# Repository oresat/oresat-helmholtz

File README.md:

# OreSat Helmholtz Cage

This repo contains design and operating instructions of a Helmholtz Cage, which uses the [Biot Savart Law](https://en.wikipedia.org/wiki/Biot%E2%80%93Savart_law) to get a desired magnetic field inside of an enclosed space using three pairs of perpendicular coils, one pair for each axis. Our fundamental purpose in doing this is to test cubesats' pointing and detumbling capabilities in LEO.

v2.0 is now underway, utilizing less hardware than v1.0. This is excellent news for everyone involved, as less parts means less things that can and will break. We are using a Raspberry Pi Pico to run it, with each set of coils getting their own motor driver, to drive the current, and a INA226 to monitor the current. A full schematic can be found [here](./controller-v2/helmholtz-controller-v2.kicad_sch). A PCB layout is in the works.

# Design Notes

**Status, design, and testing information can be found in the [OreSat Helmholtz Cage Design Notes](https://docs.google.com/document/d/1s9UlxD-V_3-_QfmXqKaY5oYsfC2GDHxeAkWD0VgjS5g/edit?tab=t.0).**

A seperate doc on the structure and design of the cage itself can be found [here](./docs/Open%20Source%20Document.docx). This doc is a bit out of date in some aspects, mainly the technical hardware, but serves as a good resource for cage construction and theory.

## Pictures
MCECS BETA Project 2018:

Current Build:

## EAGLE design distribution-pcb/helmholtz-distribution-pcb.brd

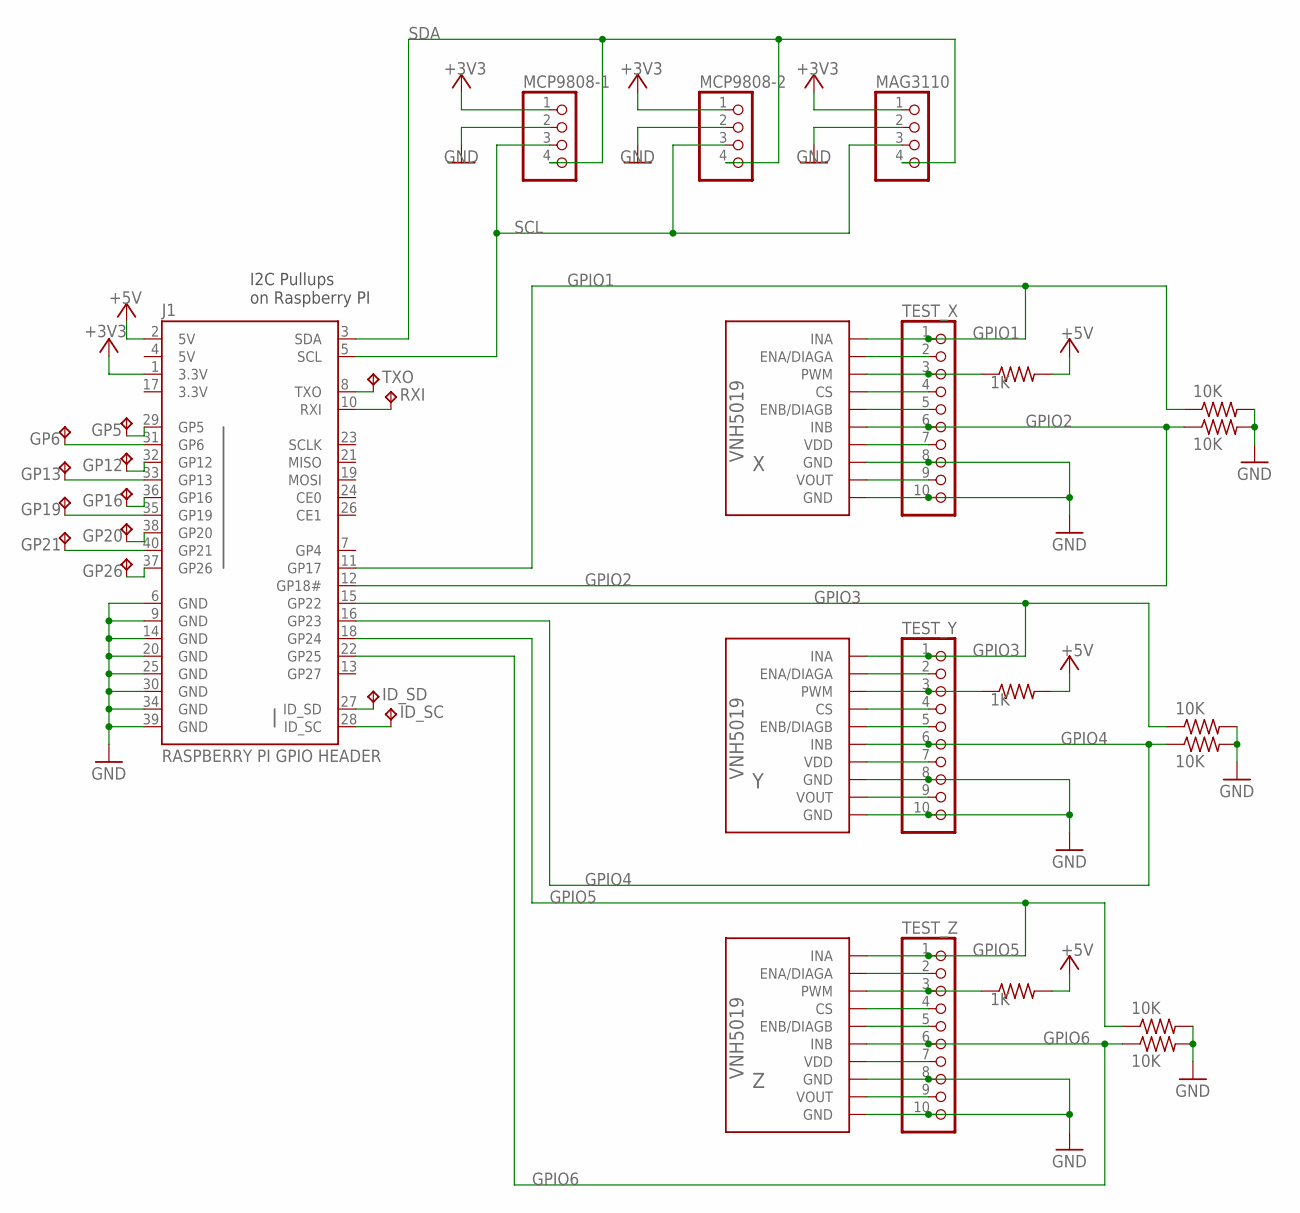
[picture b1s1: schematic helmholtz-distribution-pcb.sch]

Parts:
GP5, GP6, GP12, GP13, GP16, GP19, GP20, GP21, GP26: TPPAD1-13; P1-13
ID_SC: TPPAD1-13; P1-13
ID_SD: TPPAD1-13; P1-13
J1: RASPBERRYPI-40-PIN-GPIO_PTH; 2X20_SHROUDED
MAG3110: PINHD-1X4; 1X04
MCP9808-1, MCP9808-2: PINHD-1X4; 1X04
R2, R3, R9, R10, R16, R17: 10K; R0603
R7, R13, R20: 1K; R0603
RXI: TPPAD1-13; P1-13
TEST_X: PINHD-1X10; 1X10
TEST_Y: PINHD-1X10; 1X10
TEST_Z: PINHD-1X10; 1X10
TXO: TPPAD1-13; P1-13
X: VNH5019
Y: VNH5019
Z: VNH5019

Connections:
3.3V: J1.17 (3.3V)
5V: J1.4 (5V)
+3V3: J1.1 (3.3V), MAG3110.1, MCP9808-1.1, MCP9808-2.1
+5V: J1.2 (5V), R7.2, R13.2, R20.2
CS_X: TEST_X.4, X.CS
CS_Y: TEST_Y.4, Y.CS
CS_Z: TEST_Z.4, Z.CS
ENA/DIAGA_X: TEST_X.2, X.ENA/DIAGA
ENA/DIAGA_Y: TEST_Y.2, Y.ENA/DIAGA
ENA/DIAGA_Z: TEST_Z.2, Z.ENA/DIAGA
ENB/DIAGB_X: TEST_X.5, X.EBN/DIAGB (ENB/DIAGB)
ENB/DIAGB_Y: TEST_Y.5, Y.EBN/DIAGB (ENB/DIAGB)
ENB/DIAGB_Z: TEST_Z.5, Z.EBN/DIAGB (ENB/DIAGB)
GND: J1.6 (GND), J1.9 (GND), J1.14 (GND), J1.20 (GND), J1.25 (GND), J1.30 (GND), J1.34 (GND), J1.39 (GND), MAG3110.2, MCP9808-1.2, MCP9808-2.2, R2.2, R3.2, R9.2, R10.2, R16.2, R17.2, TEST_X.8, TEST_X.10, TEST_Y.8, TEST_Y.10, TEST_Z.8, TEST_Z.10, X.GND@1 (GND), X.GND@2 (GND), Y.GND@1 (GND), Y.GND@2 (GND), Z.GND@1 (GND), Z.GND@2 (GND)
GPIO1: J1.11 (GP17), R17.1, TEST_X.1, X.INA
GPIO2: J1.12 (GP18#), R16.1, TEST_X.6, X.INB
GPIO3: J1.15 (GP22), R10.1, TEST_Y.1, Y.INA
GPIO4: J1.16 (GP23), R9.1, TEST_Y.6, Y.INB
GPIO5: J1.18 (GP24), R3.1, TEST_Z.1, Z.INA
GPIO6: J1.22 (GP25), R2.1, TEST_Z.6, Z.INB
unnamed: GP26.TP, J1.37 (GP26)
unnamed: GP21.TP, J1.40 (GP21)
unnamed: GP20.TP, J1.38 (GP20)
unnamed: GP19.TP, J1.35 (GP19)
unnamed: GP16.TP, J1.36 (GP16)
unnamed: GP13.TP, J1.33 (GP13)
unnamed: GP12.TP, J1.32 (GP12)
unnamed: GP6.TP, J1.31 (GP6)
unnamed: GP5.TP, J1.29 (GP5)
unnamed: J1.8 (TXO), TXO.TP
unnamed: J1.10 (RXI), RXI.TP
unnamed: ID_SD.TP, J1.27 (ID_SD)
unnamed: ID_SC.TP, J1.28 (ID_SC)
PWM_X: R20.1, TEST_X.3, X.PWM
PWM_Y: R13.1, TEST_Y.3, Y.PWM
PWM_Z: R7.1, TEST_Z.3, Z.PWM
SCL: J1.5 (SCL), MAG3110.3, MCP9808-1.3, MCP9808-2.3
SDA: J1.3 (SDA), MAG3110.4, MCP9808-1.4, MCP9808-2.4
VDD_X: TEST_X.7, X.VDD
VDD_Y: TEST_Y.7, Y.VDD
VDD_Z: TEST_Z.7, Z.VDD
VOUT_X: TEST_X.9, X.VOUT
VOUT_Y: TEST_Y.9, Y.VOUT
VOUT_Z: TEST_Z.9, Z.VOUT

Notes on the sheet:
RASPBERRY PI GPIO HEADER
I2C Pullups on Raspberry PI

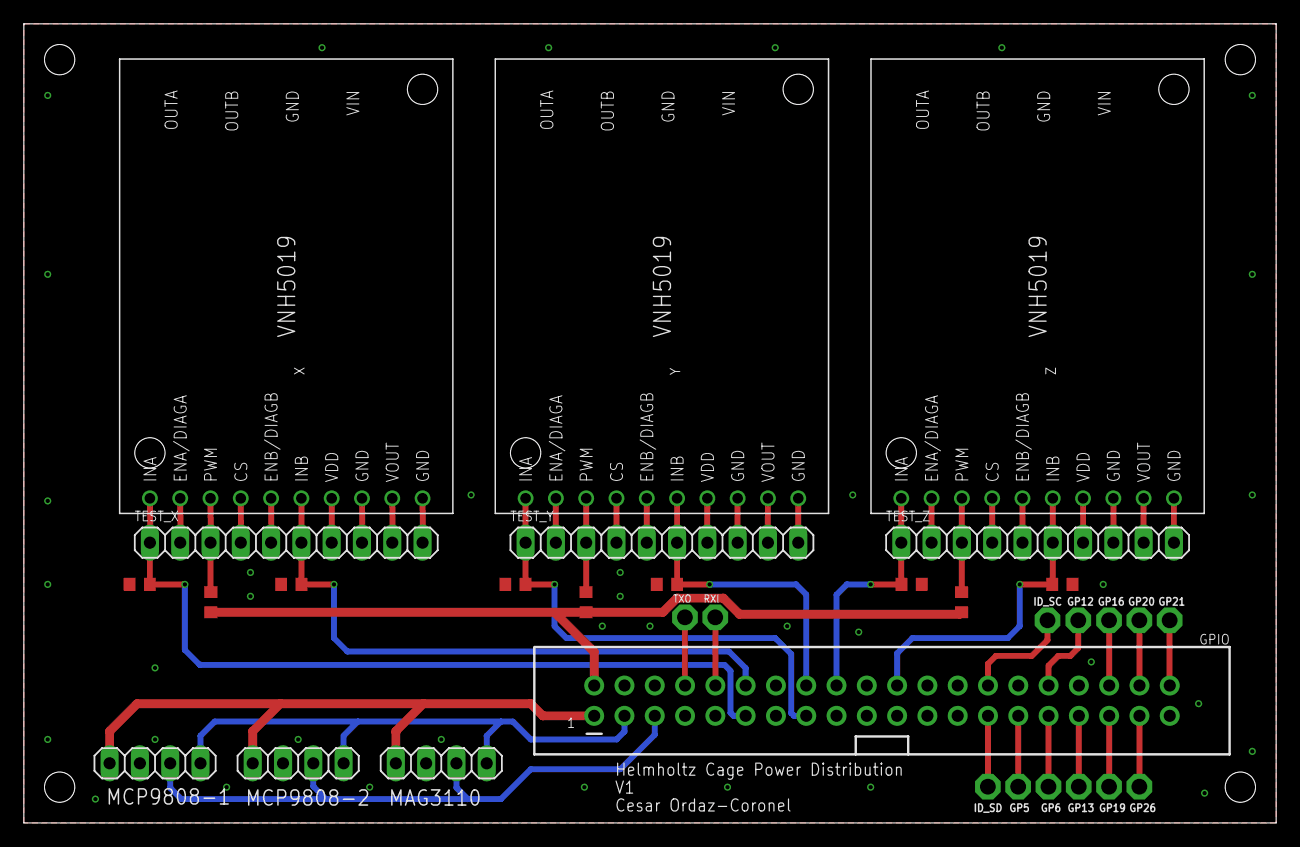
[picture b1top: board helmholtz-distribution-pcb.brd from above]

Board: 2 copper layers, 105.0 x 67.0 mm, 32 parts (0 on the bottom side), 42 nets.

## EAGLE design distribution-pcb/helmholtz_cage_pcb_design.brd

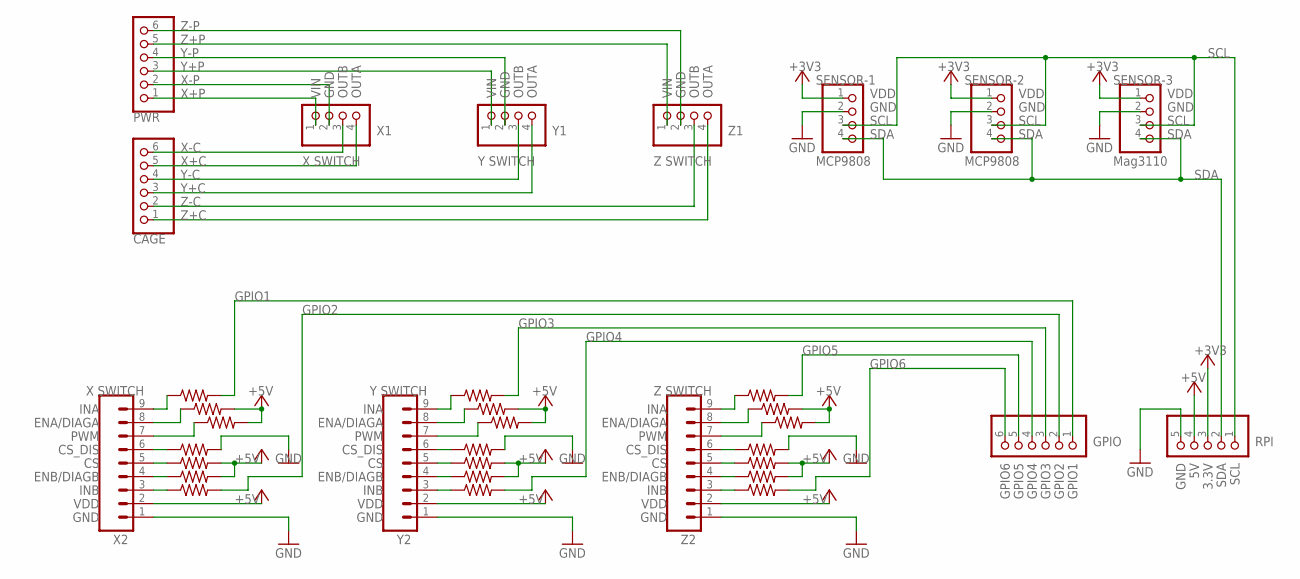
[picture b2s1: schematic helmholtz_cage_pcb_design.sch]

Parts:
CAGE: PINHD-1X6; 1X06
GPIO: PINHD-1X6; 1X06
PWR: PINHD-1X6; 1X06
R1, R2, R3, R4, R5, R6, R7, R8, R9, R10, R11, R12, R13, R14, R15, R16, R17, R18, R19, R20, R21: R-US_0204/7; 0204/7
RPI: PINHD-1X5; 1X05
SENSOR-1, SENSOR-2, SENSOR-3: PINHD-1X4; 1X04
X1: PINHD-1X4; 1X04
X2: CONN_09; 1X09
Y1: PINHD-1X4; 1X04
Y2: CONN_09; 1X09
Z1: PINHD-1X4; 1X04
Z2: CONN_09; 1X09

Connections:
+3V3: RPI.3, SENSOR-1.1, SENSOR-2.1, SENSOR-3.1
+5V: R3.2, R4.2, R5.2, R7.2, R8.2, R10.2, R11.2, R12.2, R17.2, R18.2, R19.2, R21.2, RPI.4, X2.2, Y2.2, Z2.2
CSX: R7.1, X2.5
CSY: R8.1, Y2.5
CSZ: R21.1, Z2.5
DISX: R6.1, X2.6
DISY: R9.1, Y2.6
DISZ: R20.1, Z2.6
ENAX: R3.1, X2.8
ENAY: R12.1, Y2.8
ENAZ: R17.1, Z2.8
ENBX: R4.1, X2.4
ENBY: R11.1, Y2.4
ENBZ: R18.1, Z2.4
GND: R6.2, R9.2, R20.2, RPI.5, SENSOR-1.2, SENSOR-2.2, SENSOR-3.2, X2.1, Y2.1, Z2.1
GPIO1: GPIO.1, R1.2
GPIO2: GPIO.2, R2.2
GPIO3: GPIO.3, R14.2
GPIO4: GPIO.4, R13.2
GPIO5: GPIO.5, R15.2
GPIO6: GPIO.6, R16.2
PWMX: R5.1, X2.7
PWMY: R10.1, Y2.7
PWMZ: R19.1, Z2.7
RGP1: R1.1, X2.9
RGP2: R2.1, X2.3
RGP3: R14.1, Y2.9
RGP4: R13.1, Y2.3
RGP5: R15.1, Z2.9
RGP6: R16.1, Z2.3
SCL: RPI.1, SENSOR-1.3, SENSOR-2.3, SENSOR-3.3
SDA: RPI.2, SENSOR-1.4, SENSOR-2.4, SENSOR-3.4
X+C: CAGE.5, X1.4
X+P: PWR.1, X1.1
X-C: CAGE.6, X1.3
X-P: PWR.2, X1.2
Y+C: CAGE.3, Y1.4
Y+P: PWR.3, Y1.1
Y-C: CAGE.4, Y1.3
Y-P: PWR.4, Y1.2
Z+C: CAGE.1, Z1.4
Z+P: PWR.5, Z1.1
Z-C: CAGE.2, Z1.3
Z-P: PWR.6, Z1.2

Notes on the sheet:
VIN
GND
OUTB
OUTA
X SWITCH
Y SWITCH
Z SWITCH
MCP9808
Mag3110
INA
ENA/DIAGA
PWM
CS_DIS
ENB/DIAGB
INB
VDD
SCL
SDA
GPIO1
GPIO2
GPIO3
GPIO4
GPIO5
GPIO6
3.3V

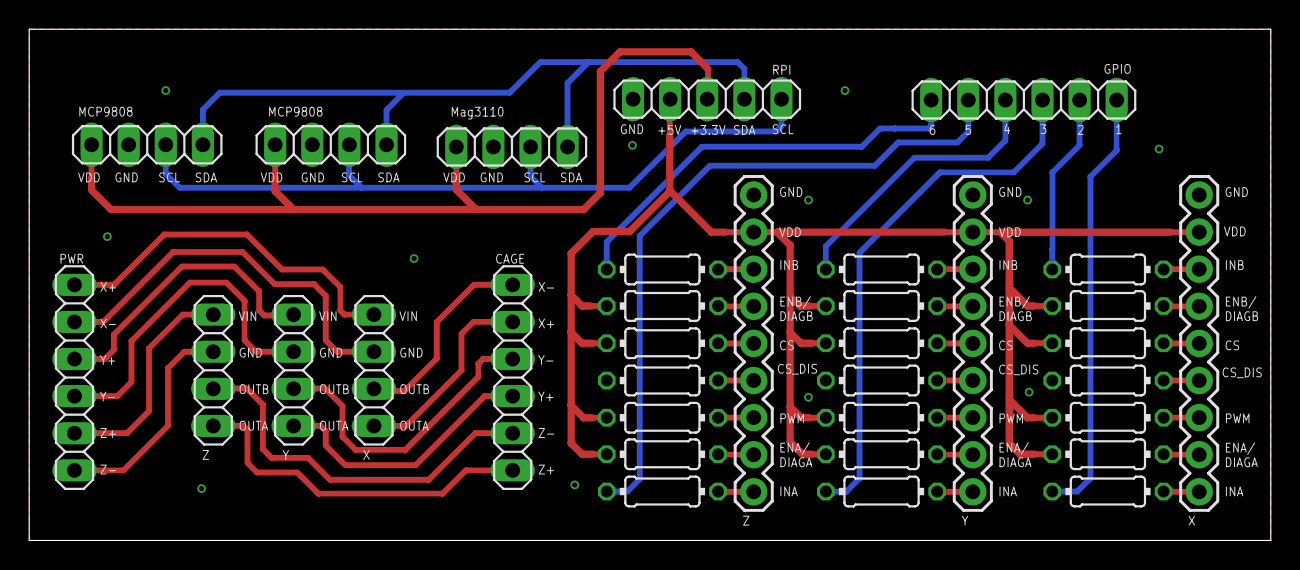
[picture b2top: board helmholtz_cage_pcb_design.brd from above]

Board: 2 copper layers, 85.0 x 35.0 mm, 34 parts (0 on the bottom side), 44 nets.

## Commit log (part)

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2019-05-02 fixed psu indexing issue
2019-05-02 anonymous update
2019-09-11 testing new functionality for motor drivers and automatic current setting
2019-09-12 bug fixin
2019-09-13 added sensor reset for magnetometer
2019-10-30 Added Cesar's first version of the distributution board.
2020-01-26 Added mounting holes to VNH boards, put mounting holes on board, and changed font to vector.
2023-01-13 Updated
    Updated with previous edits to remove unnecessary branches.
2023-01-28 Add git hooks
2023-01-28 Add Github Workflows
2023-02-13 Update license to the correct edition: GPLv3
2023-02-19 wrote serial_test.py; should open serial connections to the three PSU's, adjust their voltage and limits and close the connections
2023-02-19 adjusted settings import
2023-02-19 rewrote so that program is killable and reads voltages to screen
2023-05-15 ZXY6005s powersupply library prototype
2023-06-21 Arduino driver WIP
2023-06-23 Arduino Driver WIP v2.3
2023-06-29 Updated Arduino Nano code.
2023-08-03 Powersupply driver
2023-08-04 Reorganized Helmholtz source code files
2023-08-11 Updated Arduino driver v2.5
2023-08-14 Updated Arduino object constructor and main constructor.
2023-08-14 Updated main to work with updated Arduino driver. Removed properties and made them functions.
2023-08-14 Updated psu power function in main.
2023-08-16 Fixed an issue with ZXY6005s return voltage function.
2023-08-21 Rewrote commands for ZXY and changed a mode function.
2023-08-21 Fully functional HC shell. Fixed all bugs
2023-09-14 Added Calibration function help message. WIP
2023-09-14 Fixed typo
2023-09-14 Fixed for loop issues
2024-03-07 Test infrastructure working
    Hardcoded paths to the ttys for the psus is currently required in the
    testing infrastructure. We need to add a fixture to find the devices
    instead of hardcoding them.
    oresat_helmholtz/psu.py is the basis of the rework. Other files under
    oresat_helmholtz/ will likely be removed.
2024-03-07 Add contrib guide
    Add stubs for further documentation, including instructions for linting,
    testing, and installing dependencies needed for development.
2024-07-09 Cleaned up and updated to modern Linux
2024-07-15 added port mapping instructions to readme
2024-07-19 Added serial message on boot and started remove stupid decimal number magic numbers.
2024-07-23 Uncommented magnetometer lines to enable reading in field data.
2024-07-23 set default current and voltage
2024-07-25 commenting out magnetometer stuff... again
2024-08-07 Commented line 329.
2024-08-21 Updated the Helmholtz shell to include helper functions for the new Magnetometer library
2024-08-21 Modified main file to include draft 1 of magnetometer
2024-08-21 Adding the meter USB location as a required argument
2024-08-21 Added missing 'Magnetometer' argument on line 17
2024-08-22 Added missing parameter in meter properties function
2024-08-22 Missing parameter added to the parse_meter_response function
2024-08-22 Changed the value of ID_METER_PROP to a int, not a str.
2024-08-22 Third command draft.
2024-08-23 Draft function for streaming data.
2024-08-27 modified 'parse_data_point()' to print data value as a signed float32
2024-08-27 Prototype parsing data points function. Avoids printing bogus readings.
2024-08-27 address garbage vals avter sleep
2024-08-27 break if garbage readings
2024-08-28 New function added to calculate the average readings of all 3 axes.
2024-08-28 Fixed an issue where the chunk array wasn't defined properly.
2024-08-29 Missing variables for axes average values added.
2024-08-29 Pushing to fix bugs.
2024-08-29 Debug v2
2024-08-29 Reverting back to v2.
2024-08-29 Changing conditional parameters
2024-08-29 average data without garbage
2024-08-29 formatting averaging function
2024-08-29 Created new utilities library. Moved the reading average function into new file.
2024-08-29 Same as last revision
2024-08-29 Begin working on function to zero out the mag. field inside the cage.
2024-08-30 Added 'set_field_vector()' to Helmholtz shell
2024-08-30 Debugging 1
2024-08-30 Fixing array dimensions in utils
2024-08-30 Update PSU calls to use floats
2024-08-30 quick fix again
2024-09-03 removing superfluous comments
2024-09-03 add missing arg
2024-09-03 Added Daniel M.'s code for testing.
2024-09-03 Used square brackets instead of parenthesis
2024-09-03 Debugging target output issue in 'set_field_vector()' v1
2024-09-03 Debug
2024-09-05 removed usused variable
2024-09-05 add debug print statement
2024-09-05 Updating calibration function for linear regression
2024-09-17 Changed calibration function to record magnetometer readings
2024-09-17 Okay using enumerate in the for loops is the smarter way to do it.
2024-09-17 Added sign of magnetometer value
2024-09-20 Updated function arguments and their defaults Added constants `MAG_CURRENT_SLOPE` and `WMM_AMBIENT_FIELD` to use as default conversion factors Added constant `MAX_OUT_CURRENT` used to limit the outpu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
2024-09-20 Move new content to img
2024-09-21 Update README.md
    Updated Photo of the Helmholtz Cage
2024-09-21 Update README.md
    One more time!
2024-09-21 Major update to add manpages for software docs Added arduino.md, hshell.md, magmeter.md, powsups.md, utils.md, and manindex.rst to document HC controller Updated index.rst to include new manpages Upd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
2024-09-21 Major update filling out all function documentation Added documentation for each function in arduino.md, hshell.md, magmeter.md, powsups.md, and utils.md Updated manindex.rst
2024-09-22 Fix indentation mistake
2024-09-24 Added a function to test out Lev's basilisk code.
2024-09-25 Added a function to test our Lev's basilisk code. Replicated a commit originally made by @gcotom
2024-09-26 Update buck converter bus locations
2024-09-26 whoopsie I made a typo
2024-09-26 Previously removed current correction, put it back cause we needed it.
2024-09-27 Removed power up section of set_field_vector
2024-09-27 Adding current conversion back again
2024-10-09 Restructured Serial comm functions write, create, read, send command functions are consolidated into one `send_command` function Power supply class now controls a single unit and takes a location as 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
2024-10-13 Testing, debugging, and updating code for virtual serial port.
2024-10-13 Added calibrate_axis(), is WIP but close
2024-10-13 Calibrate_axis debug
2024-10-13 calibrate_axis debug 3
2024-10-13 calibrate_axis debug again
2024-10-15 Magnetomter communication refactored
2024-10-17 Quick fix for indexing issue in data parsing function
2024-10-20 Making stream_data request data on timeout
2024-10-20 Debug 2
2024-10-20 Fixed function call for calibrate_axis
2024-10-20 debug 3
2024-10-20 Testing new error handling for PSUs
2024-10-27 Adding delays for serial streams
2024-10-27 Remove delays, debugging
2024-10-27 Fix get_value function attempt 1
2024-10-27 Remove current correction term, we may not need it
2024-10-28 Fix call to linear_regression function
2025-01-26 added testing documentation and updated image of cage
2025-03-05 Created schematic for new Helmholtz Cage power driver
2025-03-12 New branch for development of Helmholtz controller V2
2025-03-12 Improved schematic, made it more readable
2025-03-12 Remove temporary kicad files
2025-05-11 Remove merge conflict left in commit
2025-08-15 updated schematic
2025-08-19 Updated schematic & board
2025-08-25 Pre-final review
    UART still needs to be connected
2025-08-27 Final Review Ready
2025-09-13 Alert pins connected to pico
2025-09-14 Added mounting holes to schematic & connected alert pins on PCB.
2025-10-19 Rerouted 3.3v & 12v, added zones
2025-10-20 Filled out BOM
2025-12-21 Test Python scripts for v2 controller card
2026-01-07 Formatting
2026-01-07 Fix errors in INA226 driver
    There was a redefinition of a function that looks unfinished, so I
    removed them both. I assume they were supposed to set calibration
    registers with custom values, but at the moment the purpose of the
    functions were unclear because they were unutilized.
2026-01-08 Create flash script
    Without using circuitpython's recommended Mu editor it's kind of a pain
    to flash. Thus I wrote a bash script to ease the process. This will
    probably need to be a little more robust than this to work across
    everyones computers, but this is at least a start for now.
2026-01-12 Add build process to flash script and rename it to pico-flash
    Compiling to .mpy reduces code size and increases exexcution speed.
    Additionally, the script will now create a build dir if it doesnt exist
    already, make sure the required tools are installed before building, and
    make sure the pico is plugged in before flashing, exiting with an error
    if any steps fail.
2026-01-12 Fix bugs, clean syntax
2026-01-12 use adafruit's logging module, and update pyproject.toml
2026-01-12 Remove mypy support
    It's really not happy with any of this code for some reason, even though
    it's flashing. It's saying things don't exist that very well do. I don't
    want to do any labor to get it to work at the moment. Maybe someday.
2026-01-13 Change motor pins from digital to pwm
2026-01-15 Create MR3 communication bridge sub-project
    This will go on the rpi5 and handle streaming/parsing the data from the
    milligauss meter
2026-01-20 rename milligaus_meter to mr3_reader
    semantics
2026-01-20 WIP cont.
2026-01-21 Arduino and serial bridge work in progress
2026-01-22 Complete mr3_reader code initial version
2026-01-30 Delete mr3_reader/mnt
    I don't know how this got checked into git
2026-02-01 WIP: Fix mr3 read errors
2026-02-02 Remove semicolon
2026-02-02 Update pico uart driver
    We can get rid of the buffer now that we are certain about what were
    getting from the rpi5. It will always be 21 bytes, and it comes in very
    consistently now.
2026-02-02 Reset uart input buffer on error
    Allows uart to recover from errors and prevents infinite loops when
    retrying reading the bridge until success
2026-02-03 delete mr3 cobsr file
    We'll just use the same for both the mr3 and the pico
2026-02-06 WIP: p_loop continued
2026-03-13 Update to schematic
2026-03-22 getting closer to perfect
2026-03-22 Minor cleanup on DRC
2026-03-26 Some polish
2026-04-23 Helholtz cage controller v3.0, upgrade to KICad 10, new gitignore file
2026-05-25 Fix INA226 configuration
    the ina226 comes preconfigured to expect a maximum of 3.2A, but we limit
    the motor drivers to 2A, so we can configure it to expect that. Also,
    RSHUNT was at 10m ohms, which is wrong, its 100m Ohms, so we were
    getting garbage readings.
2026-05-29 Use slow decay mode
    Using slow decay mode fixes the issue with current collapsing ~50% duty
    cycle. This is achieved by pwm-ing the input that would normally be zero
    according to the truth table while keeping the input that would normally
    be high according to the truth table high. This also means we have to do
    a little math on args to the methods ie subtract the desired duty cycle
    from 100.
2026-05-29 Add set dc cli command
    This is a useful debugging command to pwm at a a certain duty cycle a
    specific motor drivers inputs and read it's current output in a loop.
2026-06-08 Restructure project, add library
    This commit moves from a flat layout to a src layout. This move should
    keep things more organized as the project grows. It also installs the
    progressbar library from adafruit. I've updated the Makefile to handle
    these changes as well.
2026-06-17 Use Less Dicts
    because dictionaries aren't ordered in this version of python, using
    them is often not very ergonomic. using lists and tuples instead greatly
    simplifies a lot of things.
    Changes:
    motor driver assemblies list,
    slopes_and_intercepts list,
2026-06-17 rename motor -> motor driver
    for clarity, it's not a motor, its just the driver

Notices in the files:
parts and their libraries:
SparkFun-Connectors: Licensing: Creative Commons ShareAlike 4.0 International - https://creativecommons.org/licenses/by-sa/4.0
